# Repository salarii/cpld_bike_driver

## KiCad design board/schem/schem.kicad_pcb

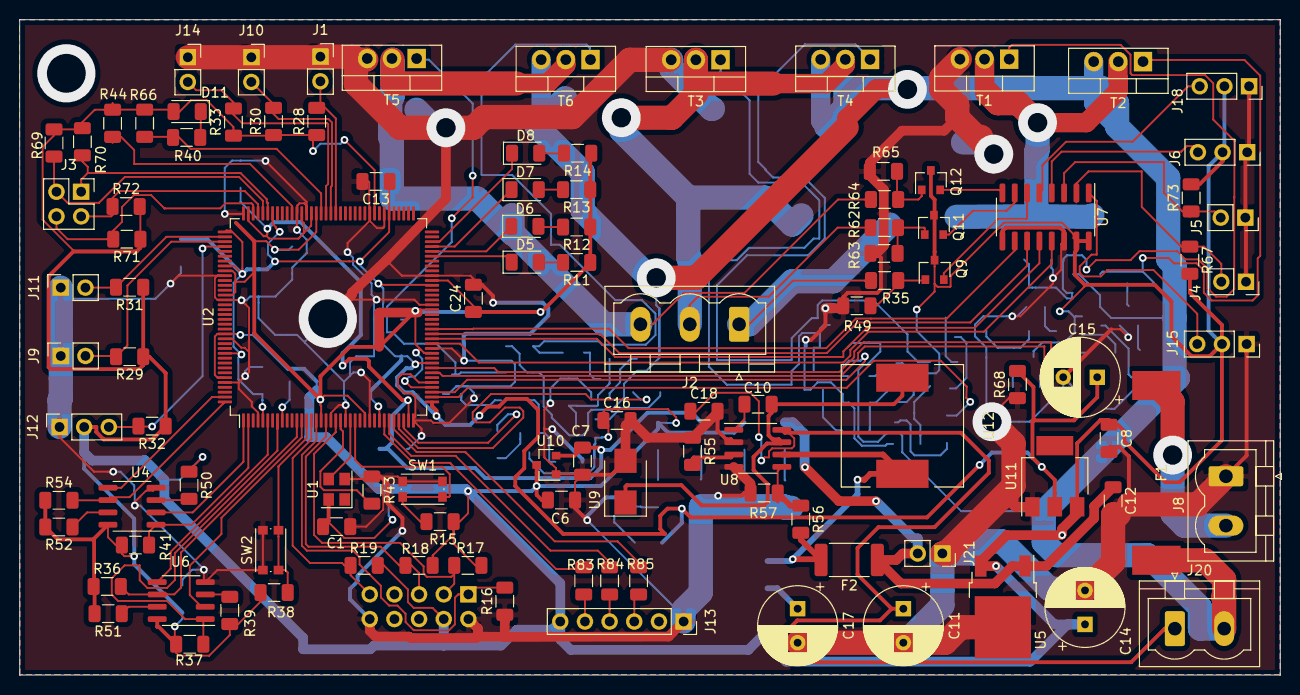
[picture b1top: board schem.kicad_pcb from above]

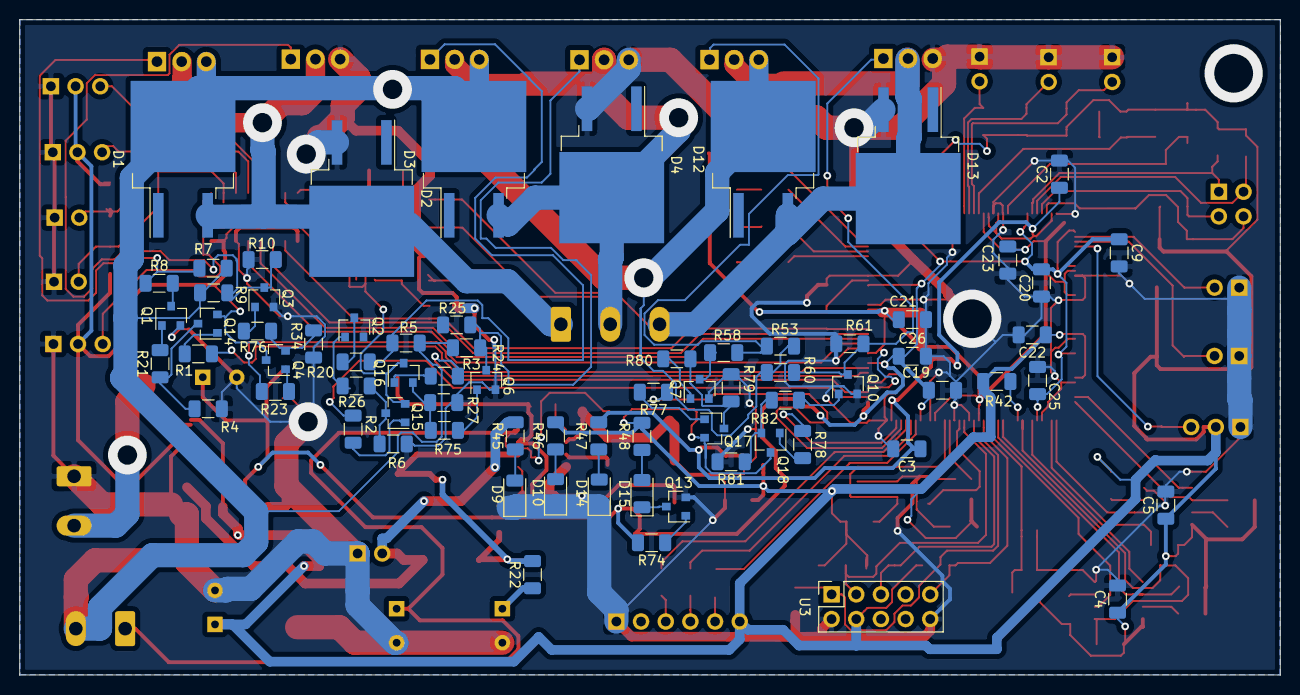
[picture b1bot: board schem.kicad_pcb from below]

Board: 2 copper layers, 129.8 x 67.5 mm, 180 parts (73 on the bottom side), 119 nets.

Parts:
C1, C2, C3, C4, C5, C8, C9, C12, C13, C16, C19, C20, C21, C22, C23, C24, C25, C26: 0.1u; C_1206_3216Metric
C6, C7: 1u; C_1206_3216Metric
C10: 0.01u; C_1206_3216Metric
C11, C17: 220u; CP_Radial_D8.0mm_P3.50mm
C14, C15: 10u; CP_Radial_D8.0mm_P3.50mm
C18: 0.22u; C_1206_3216Metric
D1, D2, D3, D4, D12, D13: BYC10; TO-263-2
D5: hal_err; LED_1206_3216Metric
D6: break_trig; LED_1206_3216Metric
D7: tmp_excd; LED_1206_3216Metric
D8: diag_led; LED_1206_3216Metric
D9: 5V_led; LED_1206_3216Metric
D10: 3.3V_led; LED_1206_3216Metric
D11: done; LED_1206_3216Metric
D14: 2.5V_led; LED_1206_3216Metric
D15: 1.2V_led; LED_1206_3216Metric
F1: 50A; fuse_20mm
F2: 3A; Fuse_2512_6332Metric
J1: no_break; PinSocket_1x02_P2.54mm_Vertical
J2: motor_out; PhoenixContact_MSTBVA_2,5_3-G-5,08_1x03_P5.08mm_Vertical
J3: test; PinSocket_2x02_P2.54mm_Vertical
J4, J5: motor_tmp; PinSocket_1x02_P2.54mm_Vertical
J6, J18: adc_red1; PinSocket_1x03_P2.54mm_Vertical
J8: POWER_IN; PhoenixContact_MSTBVA_2,5_2-G-5,08_1x02_P5.08mm_Vertical
J9: break1; PinSocket_1x02_P2.54mm_Vertical
J10: no_hal; PinSocket_1x02_P2.54mm_Vertical
J11: break2; PinSocket_1x02_P2.54mm_Vertical
J12: impulse; PinSocket_1x03_P2.54mm_Vertical
J13: hal; PinSocket_1x06_P2.54mm_Vertical
J14: no_temp; PinSocket_1x02_P2.54mm_Vertical
J15: speed; PinSocket_1x03_P2.54mm_Vertical
J20: ON/OFF; PhoenixContact_MSTBVA_2,5_2-G-5,08_1x02_P5.08mm_Vertical
J21: lamp; PinSocket_1x02_P2.54mm_Vertical
Q1, Q2, Q3, Q4, Q6, Q7, Q9, Q10, Q11, Q12, Q13, Q16, Q18: BC817; SOT-23
Q14, Q15, Q17: BC807; SOT-23
R1, R2, R3, R4, R6, R21, R23, R26, R27, R34, R75, R76, R77, R78, R79, R80, R81, R82: 20k; R_1206_3216Metric
R5, R7, R10, R25, R53, R57, R61: 2k; R_1206_3216Metric
R8, R20, R58: 4.8k; R_1206_3216Metric
R9, R24, R49, R60, R63, R65: 5k; R_1206_3216Metric
R11, R12, R13, R14, R16, R40, R45, R46, R47, R48: 1k; R_1206_3216Metric
R15, R28, R29, R30, R31, R32, R33, R38, R69, R70, R71, R72, R83, R84, R85: 10k; R_1206_3216Metric
R17, R18, R19, R36, R37, R39, R41, R42, R43, R44, R50, R51, R52, R54, R66: 4.7k; R_1206_3216Metric
R22: 1; R_1206_3216Metric
R35, R62, R64: 90k; R_1206_3216Metric
R55: 63.4k; R_1206_3216Metric
R56: 10.5k; R_1206_3216Metric
R67, R73: 640; R_1206_3216Metric
R68: 120; R_1206_3216Metric
R74: 50k; R_1206_3216Metric
SW1, SW2: SW_Push; SW_Push_1P1T_NO_CK_KMR2
T1, T3, T5: CDZ44-CDI; TO-220-3_Vertical
T2, T4, T6: IRF4905; TO-220-3_Vertical
U1: CFPS-39-12M; Oscillator_SMD_Abracon_ASE-4Pin_3.2x2.5mm
U2: EP4CE6; LQFP-144_20x20mm_P0.5mm
U3: JTAG; PinSocket_2x05_P2.54mm_Vertical
U4, U6: IS25LQ; SOIC-8_3.9x4.9mm_P1.27mm
U5: LF33CDT; TO-252-2
U7: MPC3008; SOIC-16_3.9x9.9mm_P1.27mm
U8: A8498; SOIC-8_3.9x4.9mm_P1.27mm
U9: B350B; D_SMB
U10: AP2138; SOT-23
U11: LD1117; SOT-223
U12: 68u; L_12x12mm_H4.5mm

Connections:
+1V2: C9.1, C13.1, C15.1, C19.1, C20.1, C25.1, C26.1, R68.2, R74.2, U2.5, U2.29, U2.37, U2.45, U2.61, U2.78, U2.102, U2.109, U2.116, U2.134, U11.2
+2V5: C2.1, C3.1, C7.1, R47.2, U2.35, U2.94, U2.96, U2.107, U10.2
+3V3: C1.1, C4.1, C5.1, C6.1, C8.1, C14.1, C16.1, C21.1, C22.1, C23.1, C24.1, D11.2, J6.2, J12.2, J13.6, J15.2, J18.2, Q4.3, Q9.3, Q11.3, Q12.3, Q14.2, Q15.2, Q16.3, Q17.2, Q18.3, R11.1, R12.1, R13.1, R14.1, R15.1, R17.1, R18.1, R19.1, R28.1, R29.1, R30.1, R31.1, R32.1, R33.1, R36.1, R37.1, R38.1, R39.1, R41.1, R42.1, R44.1, R46.2, R48.2, R50.1, R51.2, R52.2, R54.1, R66.2, R67.2, R69.1, R70.1, R71.1, R72.2, R73.2, U1.4, U2.17, U2.26, U2.40, U2.47, U2.56, U2.62, U2.81, U2.93, U2.117, U2.122, U2.130, U2.139, U3.4, U4.8, U5.3, U6.8, U7.15, U7.16, U10.3, U11.3
+5V: C12.1, F2.1, J21.2, R45.2, U5.1
+36V: D1.2, D3.2, D12.2, F1.1, J20.2, R5.1, R7.1, R9.1, R24.1, R53.1, R60.1, T2.3, T4.3, T6.3
/DriveAndSens/A_n: R23.1, U2.44
/DriveAndSens/A_out: D1.3, D2.2, J2.1, R35.1, T1.2, T2.2
/DriveAndSens/A_p: R1.1, U2.43
/DriveAndSens/B_n: R3.1, U2.39
/DriveAndSens/B_out: D3.3, D4.2, J2.2, R62.1, T3.2, T4.2
/DriveAndSens/B_p: R2.1, U2.38
/DriveAndSens/C_n: R78.1, U2.34
/DriveAndSens/C_out: D12.3, D13.2, J2.3, R64.1, T5.2, T6.2
/DriveAndSens/C_p: R77.1, U2.33
/DriveAndSens/adc_A: Q9.2, U7.6
/DriveAndSens/adc_B: Q11.2, U7.7
/DriveAndSens/adc_C: Q12.2, U7.8
/control/A1: J3.1, R70.2, U2.103
/control/A2: J3.2, R69.2, U2.104
/control/A3: J3.3, R72.1, U2.105
/control/A4: J3.4, R71.2, U2.106
/control/ASDO: U2.6, U6.5
/control/CLKIN: U1.3, U2.23
/control/CONF_DONE: R40.1, R66.1, U2.92
/control/DATA0: U2.13, U6.2
/control/D_break: D6.1, U2.68
/control/D_diag: D8.1, U2.70
/control/D_hal: D5.1, U2.67
/control/D_tmp: D7.1, U2.69
/control/INIT_DONE: R44.2, U2.98
/control/MI_1: U2.1, U4.2
/control/MO_1: U2.143, U4.5
/control/SCK: R36.2, U2.12, U6.6
/control/SCK_1: R54.2, U2.144, U4.6
/control/TCK: R16.2, U2.16, U3.1
/control/TDI: R19.2, U2.15, U3.9
/control/TDO: R17.2, U2.20, U3.3
/control/TMS: R18.2, U2.18, U3.5
/control/adc_clk: U2.49, U7.13
/control/adc_din: U2.51, U7.11
/control/adc_dout: U2.50, U7.12
/control/brk_1: J9.2, R29.2, U2.111
/control/brk_2: J11.2, R31.2, U2.110
/control/hal_A: R83.2, U2.30
/control/hal_B: R84.2, U2.31
/control/hal_C: R85.2, U2.32
/control/nCE: R43.2, U2.21
/control/nCEO: R37.2, U2.8, U6.1
/control/nCE_1: R41.2, U2.2, U4.1
/control/nCONFIG: R38.2, SW2.2, U2.14
/control/nRES: R15.2, SW1.2, U2.24
/control/nSTATUS: R42.2, U2.9
/control/n_b: J1.2, R28.2, U2.89
/control/n_h: J10.2, R30.2, U2.90
/control/n_t: J14.2, R33.2, U2.91
/control/spare_1: J6.3, U7.4
/control/spare_2: J18.3, U7.5
/control/speed: J15.3, U7.1
/control/step: J12.3, R32.2, U2.112
/control/temp: J4.2, R67.1, U7.2
/control/temp_tran: J5.2, R73.1, U7.3
/control/~adc_cs: U2.52, U7.10
GND: C1.2, C2.2, C3.2, C4.2, C5.2, C6.2, C7.2, C8.2, C9.2, C11.2, C12.2, C13.2, C14.2, C15.2, C16.2, C17.2, C18.2, C19.2, C20.2, C21.2, C22.2, C23.2, C24.2, C25.2, C26.2, D2.3, D4.3, D9.1, D10.1, D13.3, D14.1, J1.1, J4.1, J5.1, J6.1, J8.1, J9.1, J10.1, J11.1, J12.1, J13.1, J14.1, J15.1, J18.1, J21.1, Q1.2, Q2.2, Q3.2, Q6.2, Q7.2, Q10.2, Q13.2, R4.2, R6.2, R10.2, R16.1, R25.2, R27.2, R34.2, R43.1, R49.2, R55.1, R57.1, R61.2, R63.2, R65.2, R68.1, R79.2, R81.2, SW1.1, SW2.1, T1.3, T3.3, T5.3, U1.2, U2.4, U2.19, U2.22, U2.27, U2.36, U2.41, U2.48, U2.57, U2.63, U2.79, U2.82, U2.95, U2.97, U2.108, U2.118, U2.123, U2.131, U2.140, U3.2, U3.10, U4.4, U5.2, U6.4, U7.9, U7.14, U8.2, U8.4, U9.2, U10.1, U11.1
unnamed: C10.1, U8.7, U9.1, U12.1
unnamed: C10.2, U8.1
unnamed: C11.1, C18.1, J20.1, U8.8
unnamed: C17.1, R22.1
unnamed: D5.2, R11.2
unnamed: D6.2, R12.2
unnamed: D7.2, R13.2
unnamed: D8.2, R14.2
unnamed: D9.2, R45.1
unnamed: D10.2, R46.1
unnamed: D11.1, R40.2
unnamed: D14.2, R47.1
unnamed: D15.1, Q13.3
unnamed: D15.2, R48.1
unnamed: F1.2, J8.2
unnamed: F2.2, R22.2, R56.2, U8.6, U12.2
unnamed: J13.3, R85.1
unnamed: J13.4, R84.1
unnamed: J13.5, R83.1
unnamed: Q1.1, R21.2
unnamed: Q1.3, R8.2
unnamed: Q2.1, R26.2
unnamed: Q2.3, R20.2
unnamed: Q3.1, R76.2
unnamed: Q3.3, R9.2, R10.1, T1.1
unnamed: Q4.1, R23.2
unnamed: Q4.2, R34.1, R76.1
unnamed: Q6.1, R75.2
unnamed: Q6.3, R24.2, R25.1, T3.1
unnamed: Q7.1, R80.2
unnamed: Q7.3, R58.2
unnamed: Q9.1, R35.2, R49.1
unnamed: Q10.1, R82.2
unnamed: Q10.3, R60.2, R61.1, T5.1
unnamed: Q11.1, R62.2, R63.1
unnamed: Q12.1, R64.2, R65.1
unnamed: Q13.1, R74.1
unnamed: Q14.1, R1.2
unnamed: Q14.3, R4.1, R21.1
unnamed: Q15.1, R2.2
unnamed: Q15.3, R6.1, R26.1
unnamed: Q16.1, R3.2
unnamed: Q16.2, R27.1, R75.1
unnamed: Q17.1, R77.2
unnamed: Q17.3, R79.1, R80.1
unnamed: Q18.1, R78.2
unnamed: Q18.2, R81.1, R82.1
unnamed: R7.2, R8.1, T2.1
unnamed: R5.2, R20.1, T4.1
unnamed: R39.2, U6.3
unnamed: R50.2, U4.3
unnamed: R51.1, U6.7
unnamed: R52.1, U4.7
unnamed: R53.2, R58.1, T6.1
unnamed: R55.2, U8.3
unnamed: R56.1, R57.2, U8.5

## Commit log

2020-02-10 motor driver cont.
2020-02-11 prep uart for test
2020-02-11 minor
2020-02-11 add test block
2020-02-11 minor changes
2020-03-26 some measurement stuff
2020-03-26 continue
2020-03-26 cont
2020-03-26 cont.
2020-04-02 minor changes
2020-04-02 adc_control.vhd
2020-04-07 test app start
2020-04-10 overview of setup 1
2020-04-10 add multiplication block
2020-04-10 minor fix
2020-04-12 cleanup
2020-04-14 some consideration for pedal assist
2020-04-20 flash_controller.vhd
2020-04-20 continue gui work
2020-04-23 some debugging in flash interface
2020-04-23 add flash erase
2020-04-24 some preparation for motor experiment
2020-04-25 steps toward integration of run motor functionality
2020-04-26 control
2020-04-26 debugging motor driver functionality
2020-04-26 some debugging of gui motor control functionality
2020-04-30 rework of speed functionality
2020-04-30 remove comment
2020-04-30 add tb for speed functionality, start with motor <--> uart
2020-05-02 fixes in div and start speed measurement debugging
2020-05-07 speed measurement debug
2020-05-07 work on motor
2020-05-07 fix in speed measurement
2020-05-08 uart changes
2020-05-08 adjust gui to motor data
2020-05-16 some files related to pcb
2020-05-18 some progress in board development
2020-05-18 some work on pcb
2020-05-20 add dc-dc converter to schema
2020-05-20 some work on pcb
2020-05-21 work on pcb
2020-05-31 recent changes
2020-06-04 start pid and some debug stuff
2020-06-04 preparation for pid tests
2020-06-08 introduce vendor specific stuff
2020-06-09 some minor stuff related to speed measurement
2020-06-10 work on some debug for pid functionality
2020-06-13 start stuff for controller
2020-06-15 work on regulator unit
2020-06-17 working on controller
2020-06-18 some work on adc
2020-06-19 adc testing
2020-06-19 some debugging of adc
2020-06-20 compilation errors flash functionality
2020-06-20 fixes in flash functionality
2020-06-20 some debug in erase flash functionality
2020-06-21 add comb box for adc channel choice
2020-06-21 temporary: add for adc to control unit
2020-06-22 prepare adc test
2020-06-23 some work on schematic and minor stuff in adc channel choice functionality
2020-06-25 some work with temperature calculation
2020-06-26 some work on temperature detection
2020-06-29 start control box
2020-06-29 some debug work on control box
2020-06-30 some debug in temperature regulator
2020-06-30 start moving control box into control unit
2020-07-01 move poly to adc
2020-07-01 some work on control box integration
2020-07-01 minor fix in control box
2020-07-02 work on hal control
2020-07-02 speed measurement
2020-07-02 speed related work
2020-07-03 minor in speed handling
2020-07-05 some work on pid control
2020-07-05 some work in pid regulator
2020-07-06 start speed estimator
2020-07-06 progres in req speed estimation
2020-07-07 start integration of speed estimator
2020-07-07 some work on impulse and throttle
2020-07-08 before test
2020-07-11 rework trigger
2020-07-11 complement prev
2020-07-11 some tests
2020-07-11 work on schema
2020-07-12 work on schema
2020-07-12 work on schema
2020-07-12 working on schema
2020-07-14 fix bug in schem
2020-07-15 progress in settings functionality
2020-07-15 some work on settings functionality
2020-07-16 some changes in gui related to settings
2020-07-16 minor progress in settings (gui side)
2020-07-17 some debugging in flash controller
2020-07-19 debug flash controller
2020-07-19 progress in settings management
2020-07-20 debug flash functionality
2020-07-20 minor work in settings
2020-07-21 spare some logic resources with usage of embedded multipliers
2020-07-21 minor work in gui, minor fix in embedded multiplier
2020-07-21 copy this piece of code
2020-07-21 some work in gui app
2020-07-22 try to fix issues with uart communication
2020-07-22 some work in gui
2020-07-22 minor work on uart synchronisation
2020-07-23 start develop float mul for alternative implementation
2020-07-27 minor fixes
2020-07-27 some bug fixing
2020-07-28 some work on settings
2020-07-28 work on settings
2020-07-28 minor fixes in settings
2020-07-29 settings other minor stuff
2020-07-29 adjust poly
2020-07-29 some testing
2020-07-31 minor fixes and adjustments
2020-08-03 changes in schema
2020-08-03 minor in pcb
2020-09-17 minor schema fix
2020-09-23 there is problem in (prototype) board. I need to downsample of a switching frequency. I don't know yet if this is permanent change
2020-10-02 safty and second temperature
2020-10-02 second temperature, safety
2020-10-03 safety for slow bike resign from pid
2020-10-04 add filters
2020-10-04 test speed filter
2020-10-06 some changes
2020-10-07 forget to add this
2020-10-08 some safety measures
2020-10-09 kill noise from adc when read temperature some other protection
